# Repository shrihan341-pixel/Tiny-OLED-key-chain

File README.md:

# Tiny OLED Keychain — Wandering Faces

A pocket-sized keychain concept that shows animated digital faces wandering across a directly viewed 128×64 OLED. The intended controller is a Seeed Studio XIAO ESP32-C3 SMD. The enclosure concept has a front display window, a side switch opening, a rear cover, and a keyring loop. There is no hologram or beam-splitter block in this design.

## Project status — prototype concept, not fabrication-approved

This repository is being developed as an original project. The display, battery, switch, and PCB are not yet finalized or purchased. The CAD dimensions are placeholders, the firmware needs to be configured for the chosen display controller, and the electronics have not been validated. Do not order a PCB or assemble a LiPo-powered prototype from these concept files alone.

## Intended hardware

- Seeed Studio XIAO ESP32-C3 SMD
- 1.3-inch 128×64 OLED module; confirm whether its controller is SH1106, SSD1306, or another type and verify its interface/pinout
- Single-cell LiPo battery with an appropriate, verified charging/protection arrangement
- Slide switch selected to suit the actual power path and mechanical cutout
- Custom PCB, keyring, and 3D-printed enclosure

The reference schematic/BOM shared during planning describes a 0.96-inch OLED and does not show the proposed battery or slide switch. It is not the final schematic for this 1.3-inch battery-powered design. The reference project also includes a beam-splitter cube; that part is intentionally excluded here.

## Repository map

- `BOM.csv` — proposed parts and unresolved selection/verification status
- `CAD/case.scad` — adjustable OpenSCAD enclosure concept; not a measured fit
- `CAD/README.md` — CAD assumptions and export instructions
- `PCB/README.md` — current electrical design status and required KiCad checks
- `Firmware/main.ino` — animated face demo using U8g2; display driver selection is configurable
- `Firmware/README.md` — libraries, configuration, and flash instructions
- `Production/README.md` — fabrication-readiness and safety checklist
- `PROJECT_SUMMARY.md` — concise project brief

## Build / preview

### CAD

Open `CAD/case.scad` in OpenSCAD. Set `part` to `"body"` or `"cover"`, render, then export each STL separately. Dimensions are deliberately adjustable; compare the model against the actual PCB, OLED module, battery, and switch before printing. See `CAD/README.md`.

### Firmware

Install the Arduino IDE, ESP32 board support for XIAO ESP32-C3, and the U8g2 library. Select the OLED controller in `Firmware/main.ino`, then build and test with the exact display module. See `Firmware/README.md`.

### Electronics

The repository does not yet include a finalized KiCad schematic or routed board. The available reference schematic/BOM is for a different configuration and must not be treated as manufacturing data for this project. See `PCB/README.md` before creating fabrication files.

## Fabrication review checklist

A reviewer should be able to find the native KiCad schematic and board, verified BOM, checked Gerbers/drill outputs, source CAD plus STEP/STL exports, firmware and build instructions, assembly notes, and truthful status photos or renders. At present, several of these deliverables are not complete; the checklist in `Production/README.md` records them without claiming approval.

## Attribution and scope

This is an original direct-view keychain concept, not a copy of the referenced Hologram-Keychain design. The reference was used only to understand the general organization of a hardware project. Do not include its design files, images, or BOM as if they were created for this project. Review the referenced project's license before reusing any of its materials.

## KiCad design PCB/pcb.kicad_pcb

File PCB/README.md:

# PCB / electrical design status

This folder contains a draft KiCad concept for the direct-view keychain project. It is intentionally an early concept and should not be treated as a fabrication-approved design. The exact OLED module, battery, switch, and enclosure fit have not been verified against real hardware.

## Draft design intent

- Controller: Seeed Studio XIAO ESP32-C3 SMD
- Display: 0.96-inch I2C OLED module, 4-wire header style, consistent with the reference build
- Battery: single-cell LiPo via JST or equivalent 2-pin connector
- Power path: slide switch placed in the battery path before the XIAO board input
- Form factor: compact keychain board sized for a printed case and a front display opening

## Included files

- `pcb.kicad_pro` — KiCad project metadata
- `pcb.kicad_sch` — draft electrical schematic
- `pcb.kicad_pcb` — draft board layout

## Before fabrication or submission

1. Confirm the exact OLED module datasheet and pinout.
2. Confirm battery chemistry, capacity, and charging/protection design.
3. Verify the switch and battery connector positions against the physical enclosure.
4. Run KiCad ERC and DRC.
5. Export Gerbers and a final BOM from the reviewed board.
6. Fit-check the enclosure against the assembled PCB before ordering parts.

This folder is a draft starting point, not a manufacturer-ready board.

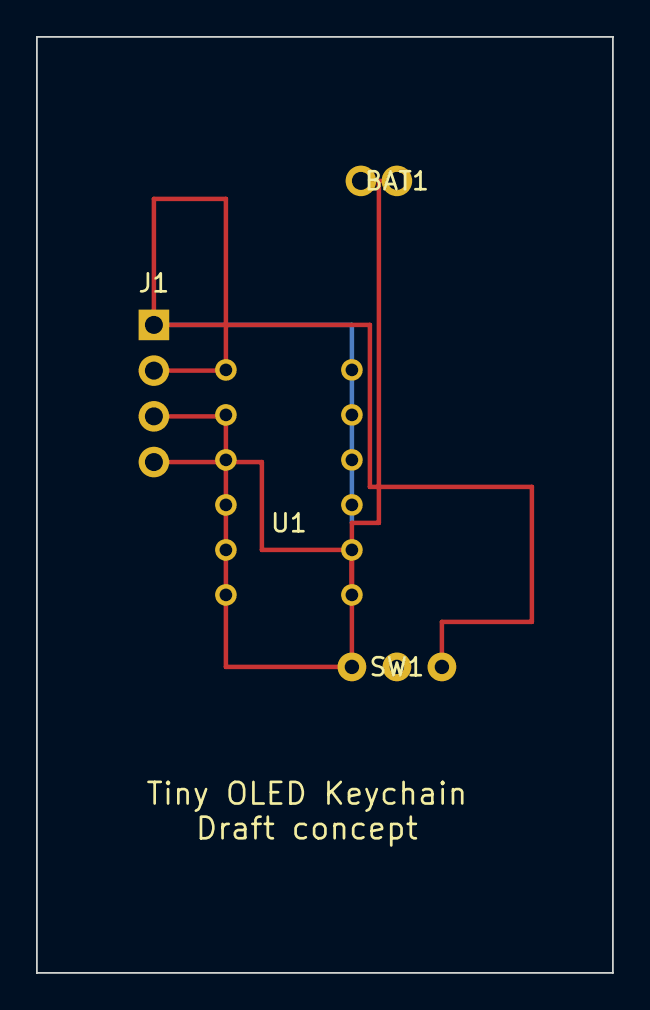
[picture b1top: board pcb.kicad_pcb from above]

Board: 2 copper layers, 32.0 x 52.0 mm, 4 parts (0 on the bottom side), 5 nets.

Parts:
BAT1: JST_2PIN; JST_PH_S2B-PH-K_1x02_P2.00mm_Horizontal
J1: OLED_4PIN; PinHeader_1x04_P2.54mm_Vertical
SW1: SW_SPDT; SW_Slide_1P2T_CK_OS102011MS2Q
U1: XIAO_ESP32C3; XIAO-ESP32C3

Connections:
+3V3: J1.1, SW1.3, U1.4, U1.8, U1.9
GND: BAT1.2, J1.4, U1.1, U1.5, U1.7, U1.10, U1.12
SCL: J1.3, U1.3
SDA: J1.2, U1.2
VBAT: BAT1.1, SW1.1, SW1.2, U1.6, U1.11
